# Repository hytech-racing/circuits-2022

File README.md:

# 2022 Circuits

Repository for all of the circuits for the 2021-2022 car.

## Getting Started with this Git Repository
1. Create a GitHub account if you don't already have one.
2. Follow HyTech's [Software Guide](https://github.com/hytech-racing/training/tree/master/Resources).
3. Download and install [GitHub Desktop](https://desktop.github.com/) (basic) or [Git CLI](https://git-scm.com/book/en/v2/Getting-Started-Installing-Git) (advanced).
    * If you are using GitHub Desktop for the first time, be sure to read the [User Guide](https://help.github.com/desktop/guides/).
    * If you are using Git for the first time, you should start off by reading a tutorial. There are many available online:
        * [Git Tutorial](https://git-scm.com/docs/gittutorial)
        * [Atlassian Git Tutorial](https://www.atlassian.com/git/tutorials/)
    * You may want to keep a copy of [GitHub's Git Cheat Sheet](https://services.github.com/kit/downloads/github-git-cheat-sheet.pdf) as a reference.
4. Talk to your subteam lead to be added to the team within the GitHub organization.
5. Clone this repository to your computer using the URLs:
    * SSH: `git@github.com:hytech-racing/circuits-2022.git`
    * HTTPS: `https://github.com/hytech-racing/circuits-2022.git`

## Getting Started with EAGLE
1. Follow HyTech's [Software Guide](https://github.com/hytech-racing/training/tree/master/Resources).
2. Download and install Autodesk [EAGLE](https://www.autodesk.com/products/eagle/overview)
3. Get the free [Educational License](https://www.autodesk.com/education/free-software/eagle) (a .edu email address is required)

## Github Software Guidelines and Electrical Designs Rules Review Process
Follow HyTech's [Github Software Guidelines](https://gtvault.sharepoint.com/:w:/r/sites/HyTechRacing2/Shared%20Documents/Electrical%20-%20All/HT06/Guidelines%20Rules%20and%20Procedures/Github%20Software%20Guidelines.docx?d=w7e0d7e36afeb47b5a935bd7a4851bceb&csf=1&web=1&e=sudzjV) to understand our development flow and pull request procedure.
Follow HyTech's [Electrical Designs Rules Review Process](https://gtvault.sharepoint.com/:w:/r/sites/HyTechRacing2/Shared%20Documents/Electrical%20-%20All/HT06/Guidelines%20Rules%20and%20Procedures/Electrical%20Designs%20Rules%20Review%20Process.docx?d=w0277498dfb4b4b9fbfad0e5db8a187c8&csf=1&web=1&e=LDFCNz) to understand circuit design flow. 

## Circuit Board Versioning Scheme
* New boards must start their numbering at revision 1.
* Revision numbers must be incremented by 1 when a physical board is manufactured, but not at any other time.
* After a board is manufactured, the files corresponding to the manufactured version should not be modified.
* Circuit boards based off of a previous year's design should increment based off of the previous board's revision number.

## More Information
* [Software Guide](https://github.com/hytech-racing/training/tree/master/Resources)
* [Team Site](https://hytechracing.gatech.edu/)
* [Facebook](https://www.facebook.com/HyTechRacing/)
* [Instagram](https://www.instagram.com/hytech.racing/)
* [Engage](https://gatech.campuslabs.com/engage/organization/hytech-racing)

## License
This project is licensed under the GPL License v3.0. See the [LICENSE](LICENSE) file for more information.

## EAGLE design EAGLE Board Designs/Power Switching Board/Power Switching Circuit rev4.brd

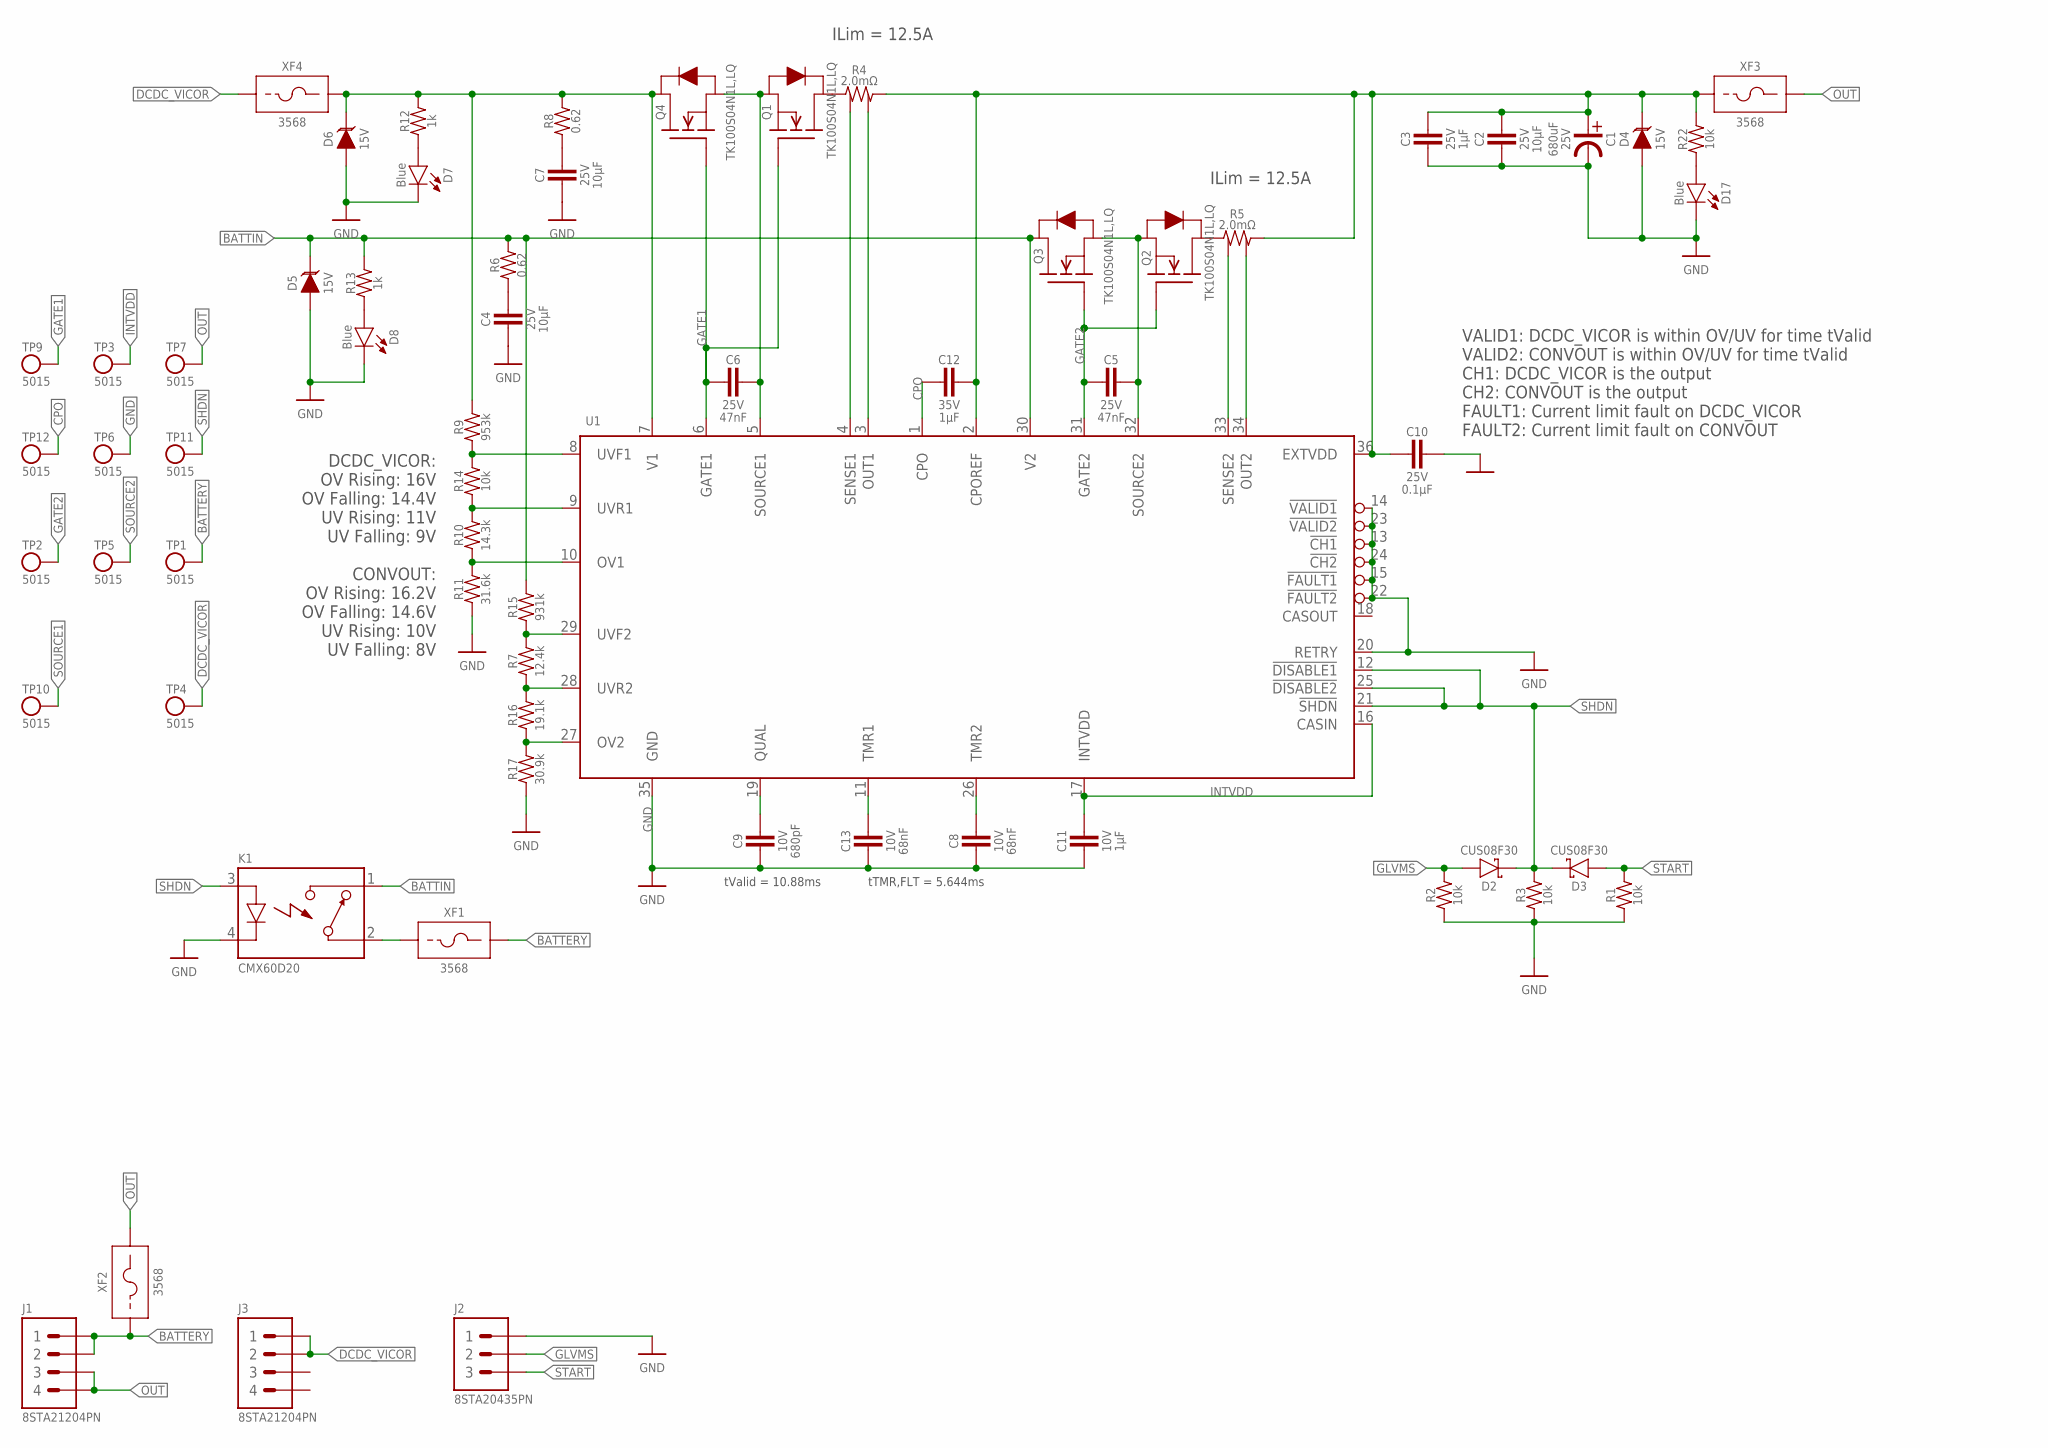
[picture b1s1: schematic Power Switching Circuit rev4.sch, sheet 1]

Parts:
C1: EEUFP1E681; EEUFP1E*
C2, C4, C7: CAPACITOR_0603_25V_10UF; 0603-CAP
C3: CAPACITOR_0603_25V_1UF; 0603-CAP
C5, C6: CAPACITOR_0603_25V_47NF; 0603-CAP
C8, C13: CAPACITOR_0603_10V_68NF; 0603-CAP
C9: CAPACITOR_0603_10V_680PF; 0603-CAP
C10: CAPACITOR_0603_25V_0.1UF; 0603-CAP
C11: CAPACITOR_0603_10V_1UF; 0603-CAP
C12: CAPACITOR_0603_35V_1UF; 0603-CAP
D2, D3: SCHOTTKY_SOD323_30V; SOD-323
D4, D5, D6: TVS_15V; SOT-23
D7, D8, D17: LED_0603_BLUE; 0603-LED
J1, J3: CONNECTOR-4_SOURIAU_; SOURIAU_12-04
J2: CONNECTOR-3_8STA20435PN; SOURIAU_04-35
K1: RELAY_SOLIDSTATE_NO_CMX60D20; CRYDOM_CMX
Q1, Q2, Q3, Q4: TRANSISTOR_N_MOS_2-7K1S_TK100S04N1LLQ; DPAK(2-7K1S)
R1, R2, R3, R14, R22: RESISTOR_0603_10K; 0603-RES
R4, R5: RESISTOR_SENSE__WSL40262L000FEB; 4026
R6, R8: RESISTOR_0805_0.62; 0805-RES
R7: RESISTOR_0603_12.4K; 0603-RES
R9: RESISTOR_0805_953K; 0805-RES
R10: RESISTOR_0805_14.3K; 0805-RES
R11: RESISTOR_0805_31.6K; 0805-RES
R12, R13: RESISTOR_0603_1K; 0603-RES
R15: RESISTOR_0805_931K; 0805-RES
R16: RESISTOR_0805_19.1K; 0805-RES
R17: RESISTOR_0603_30.9K; 0603-RES
TP1, TP2, TP4, TP5, TP6, TP7, TP9, TP10, TP11, TP12: TEST_POINT; 5015
TP3: INTVDD; 5015
U1: LTC4421; SSOP-36
XF1, XF2, XF3, XF4: FUSE_HOLDER_MINIBLADEPTH; 3568

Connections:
!SHDN: D2.C, D3.C, K1.3 (CONTROL+), R3.2, TP11.1, U1.12 (!DISABLE1), U1.21 (!SHDN), U1.25 (!DISABLE2)
BATTERY: J1.1, J1.2, TP1.1, XF1.3 (2), XF1.4 (2), XF2.1, XF2.2 (1)
BATTIN: D5.3 (C), K1.1 (CONTACT2), Q3.2 (D), R6.2, R13.2, R15.2, U1.30 (V2)
CPO: C12.2, TP12.1, U1.1 (CPO)
DCDC_VICOR: J3.1, J3.2, TP4.1, XF4.1, XF4.2 (1)
DCDC_VICORPREMOS: D6.3 (C), Q4.2 (D), R8.2, R9.2, R12.2, U1.7 (V1), XF4.3 (2), XF4.4 (2)
GATE1: C6.2, Q1.1 (G), Q4.1 (G), TP9.1, U1.6 (GATE1)
GATE2: C5.2, Q2.1 (G), Q3.1 (G), TP2.1, U1.31 (GATE2)
GLVMS: D2.A, J2.B (2), R2.2
GND: C1.P$2 (MINUS), C2.2, C3.2, C4.2, C7.2, C8.2, C9.2, C10.1, C11.2, C13.2, D4.1 (A), D5.1 (A), D6.1 (A), D7.1 (C), D8.1 (C), D17.1 (C), J2.A (1), K1.4 (CONTROL-), R1.1, R2.1, R3.1, R11.1, R17.1, TP6.1, U1.13 (!CH1), U1.14 (!VALID1), U1.15 (!FAULT1), U1.20 (RETRY), U1.22 (!FAULT2), U1.23 (!VALID2), U1.24 (!CH2), U1.35 (GND)
INTVDD: C11.1, TP3.1, U1.16 (CASIN), U1.17 (INTVDD)
unnamed: C9.1, U1.19 (QUAL)
unnamed: C13.1, U1.11 (TMR1)
unnamed: C8.1, U1.26 (TMR2)
unnamed: C4.1, R6.1
unnamed: D17.2 (A), R22.1
unnamed: D8.2 (A), R13.1
unnamed: D7.2 (A), R12.1
unnamed: K1.2 (CONTACT1), XF1.1, XF1.2 (1)
unnamed: R5.3, U1.33 (SENSE2)
unnamed: R5.4, U1.34 (OUT2)
unnamed: C7.1, R8.1
unnamed: R4.3, U1.4 (SENSE1)
unnamed: R10.2, R14.1, U1.9 (UVR1)
unnamed: R10.1, R11.2, U1.10 (OV1)
unnamed: R7.2, R15.1, U1.29 (UVF2)
unnamed: R7.1, R16.2, U1.28 (UVR2)
unnamed: R16.1, R17.2, U1.27 (OV2)
unnamed: Q2.2 (D), R5.1
unnamed: R4.4, U1.3 (OUT1)
unnamed: Q1.2 (D), R4.1
OUT: J1.3, J1.4, TP7.1, XF2.3 (2), XF2.4 (2), XF3.3 (2), XF3.4 (2)
OUTPREFUSE: C1.P$1 (PLUS), C2.1, C3.1, C10.2, C12.1, D4.3 (C), R4.2, R5.2, R22.2, U1.2 (CPOREF), U1.36 (EXTVDD), XF3.1, XF3.2 (1)
SOURCE1: C6.1, Q1.3 (S), Q4.3 (S), TP10.1, U1.5 (SOURCE1)
SOURCE2: C5.1, Q2.3 (S), Q3.3 (S), TP5.1, U1.32 (SOURCE2)
START: D3.A, J2.C (3), R1.2
UVF1: R9.1, R14.2, U1.8 (UVF1)

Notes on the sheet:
DCDC_VICOR: OV Rising: 16V OV Falling: 14.4V UV Rising: 11V UV Falling: 9V CONVOUT: OV Rising: 16.2V OV Falling: 14.6V UV Rising: 10V UV Falling: 8V
tValid = 10.88ms
tTMR,FLT = 5.644ms
ILim = 12.5A
VALID1: DCDC_VICOR is within OV/UV for time tValid VALID2: CONVOUT is within OV/UV for time tValid CH1: DCDC_VICOR is the output CH2: CONVOUT is the output FAULT1: Current limit fault on DCDC_VICOR FAULT2: Current limit fault on CONVOUT

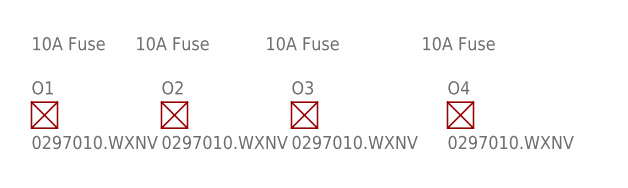
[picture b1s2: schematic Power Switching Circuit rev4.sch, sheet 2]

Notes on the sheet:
10A Fuse

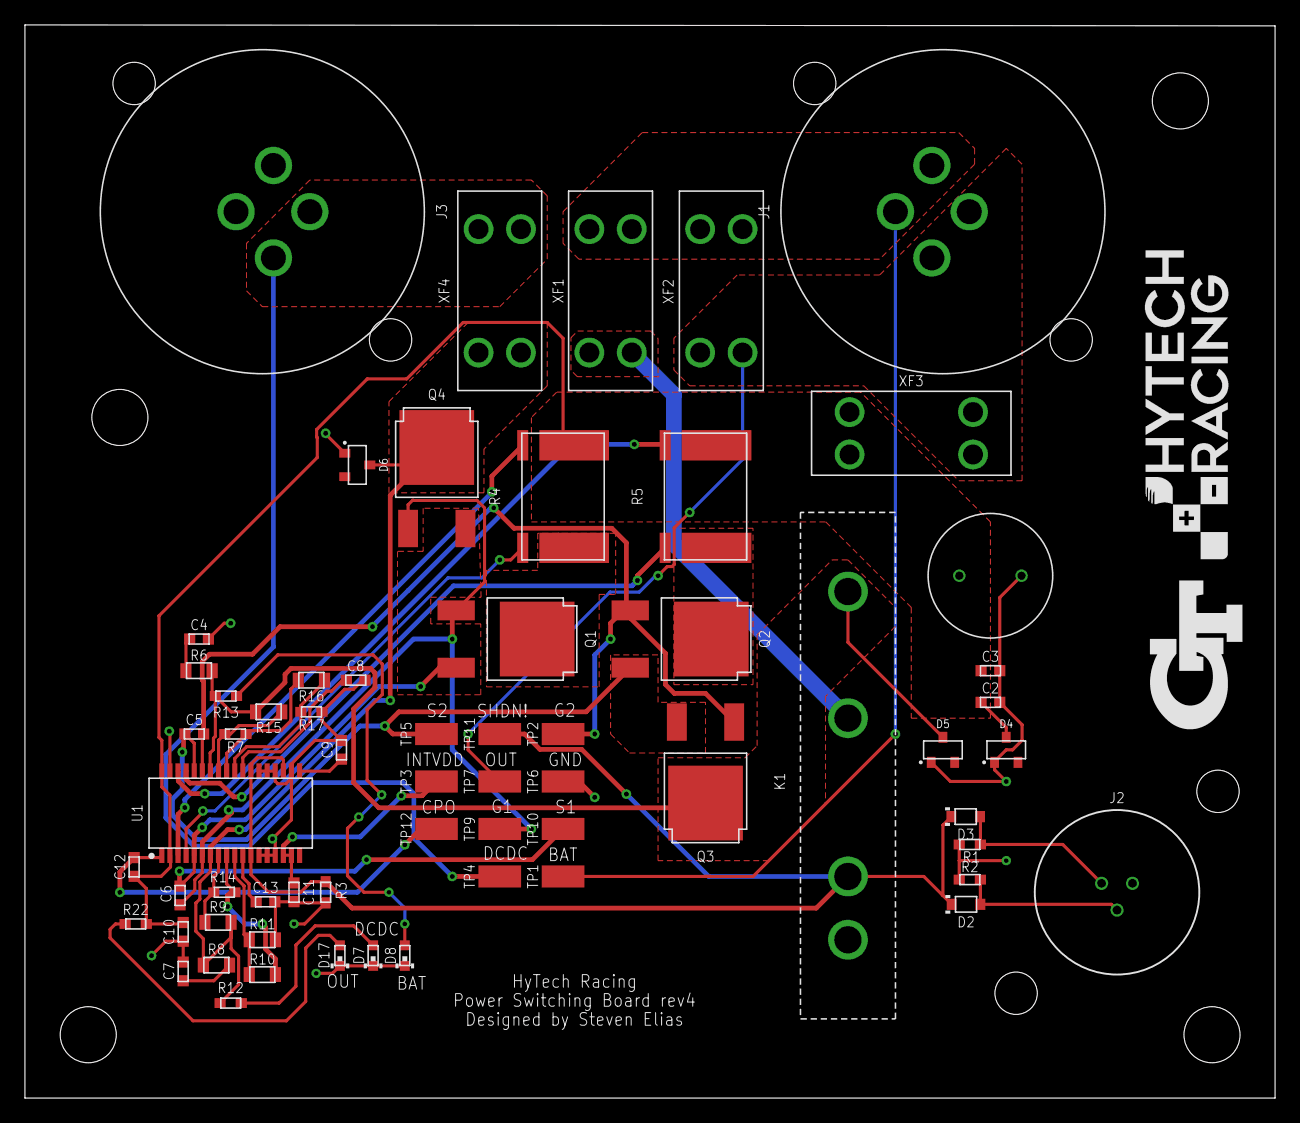
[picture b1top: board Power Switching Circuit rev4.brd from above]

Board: 2 copper layers, 100.3 x 86.1 mm, 69 parts (0 on the bottom side), 37 nets.

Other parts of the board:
U$1: LOGO_GT_MEDIUM
U$2: LOGO_HYTECH_MEDIUM
U$3, U$4, U$5, U$6: MOUNTING_M4

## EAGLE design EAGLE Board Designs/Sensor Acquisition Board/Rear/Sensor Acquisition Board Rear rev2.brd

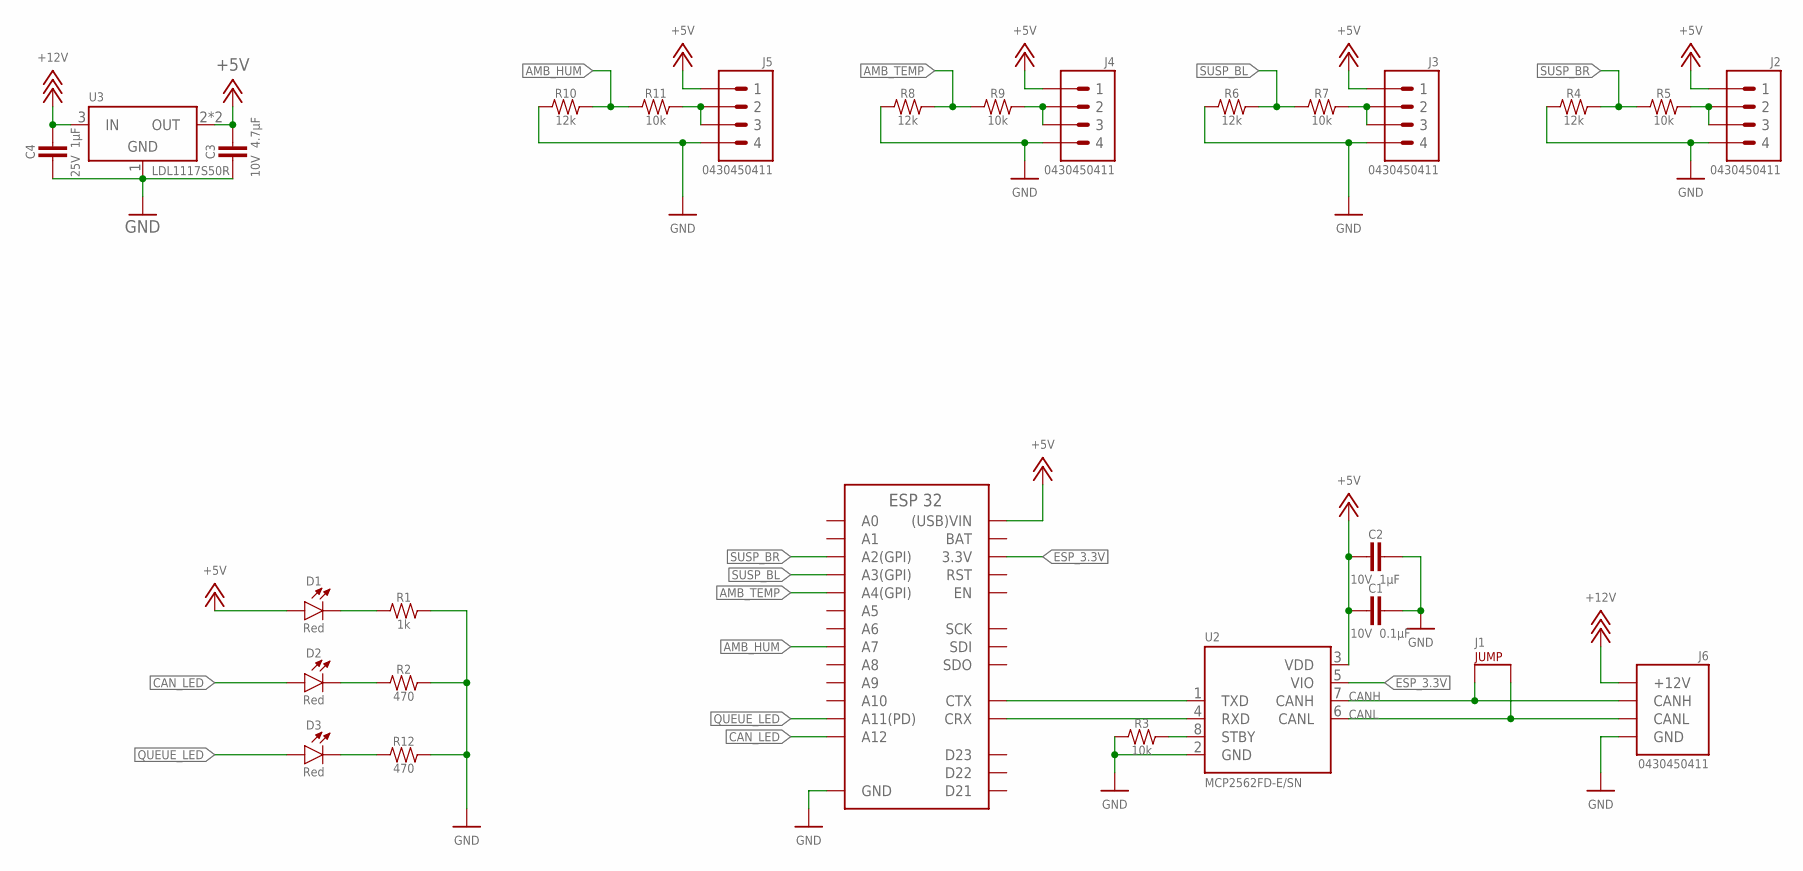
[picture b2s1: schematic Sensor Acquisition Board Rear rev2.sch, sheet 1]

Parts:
A2: ESP32
C1: CAPACITOR_0603_10V_0.1UF; 0603-CAP
C2: CAPACITOR_0603_10V_1UF; 0603-CAP
C3: CAPACITOR_0603_10V_4.7UF; 0603-CAP
C4: CAPACITOR_0603_25V_1UF; 0603-CAP
D1, D2, D3: LED_0603_RED; 0603-LED
J1: JUMPER_0603_; 0603-RES
J2, J3, J4, J5: CONNECTOR-4_μF_S_RA_; MOLEX_MICROFIT_SMD_RIGHTANGLE_04_DUAL
J6: CONNECTOR-CAN_μF_S_RA_; MOLEX_MICROFIT_SMD_RIGHTANGLE_04_DUAL
R1: RESISTOR_0603_1K; 0603-RES
R2, R12: RESISTOR_0603_470; 0603-RES
R3, R5, R7, R9, R11: RESISTOR_0603_10K; 0603-RES
R4, R6, R8, R10: RESISTOR_0603_12K; 0603-RES
U2: MCP2562FD; SOIC-08(NARROW,0.15")
U3: VOLTAGE_REGULATOR_SOT-223_5V; SOT-223

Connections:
+5V: A2.USB ((USB)VIN), C1.2, C2.2, C3.1, D1.2 (A), J2.1, J3.1, J4.1, J5.1, U2.3 (VDD), U3.2 (OUT), U3.4 (OUT)
+12V: C4.1, J6.1 (+12V), U3.3 (IN)
AMB_HUM: A2.D32 (A7), R10.2, R11.1
AMB_TEMP: A2.A4 (A4(GPI)), R8.2, R9.1
BAT: A2.BAT
CANH: J1.1, J6.4 (CANH), U2.7 (CANH)
CANL: J1.2, J6.3 (CANL), U2.6 (CANL)
CAN_LED: A2.D13 (A12), D2.2 (A)
EN: A2.EN
ESP_3.3V: A2.3.3V, U2.5 (VIO)
GND: A2.GND, C1.1, C2.1, C3.2, C4.2, J2.4, J3.4, J4.4, J5.4, J6.2 (GND), R1.2, R2.2, R3.1, R4.1, R6.1, R8.1, R10.1, R12.2, U2.2 (GND), U3.1 (GND)
unnamed: D1.1 (C), R1.1
unnamed: D2.1 (C), R2.1
unnamed: R3.2, U2.8 (STBY)
unnamed: A2.TX (CTX), U2.1 (TXD)
unnamed: J2.2, J2.3, R5.2
unnamed: J4.2, J4.3, R9.2
unnamed: J3.2, J3.3, R7.2
unnamed: A2.RX (CRX), U2.4 (RXD)
unnamed: J5.2, J5.3, R11.2
unnamed: D3.1 (C), R12.1
QUEUE_LED: A2.D12 (A11(PD)), D3.2 (A)
RST: A2.RST
SUSP_BL: A2.A3 (A3(GPI)), R6.2, R7.1
SUSP_BR: A2.A2 (A2(GPI)), R4.2, R5.1

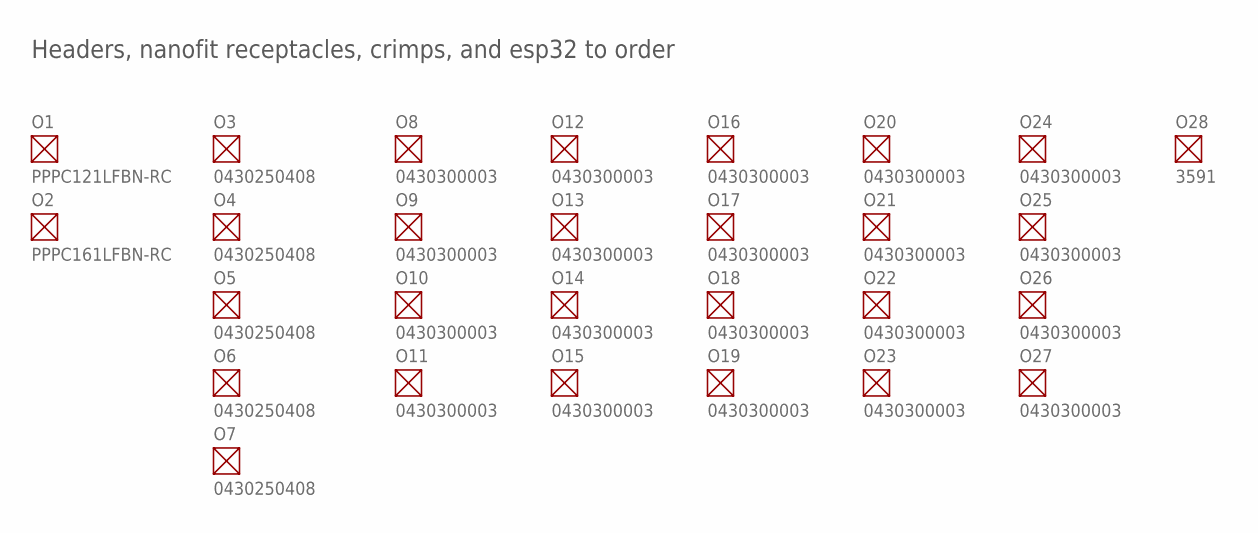
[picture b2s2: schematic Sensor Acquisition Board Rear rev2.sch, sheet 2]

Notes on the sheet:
Headers, nanofit receptacles, crimps, and esp32 to order

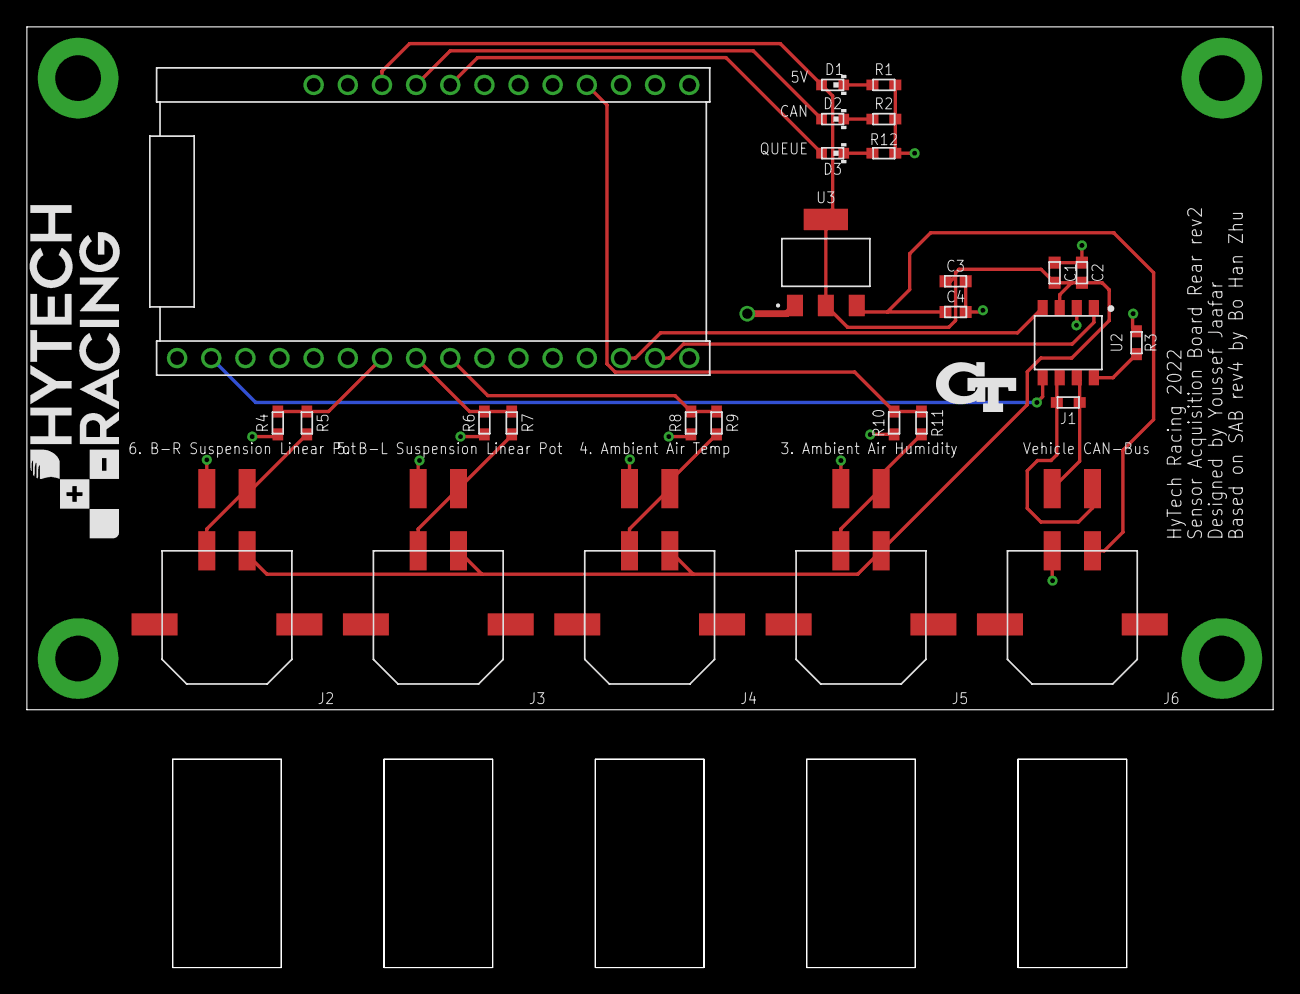
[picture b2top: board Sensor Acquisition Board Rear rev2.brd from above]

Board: 2 copper layers, 92.7 x 50.8 mm, 34 parts (0 on the bottom side), 22 nets.

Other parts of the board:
$$U$6: MOUNTING_M3
U$1, U$2, U$5: MOUNTING_M3
U$3: LOGO_GT_0.25"
U$4: LOGO_HYTECH_MEDIUM

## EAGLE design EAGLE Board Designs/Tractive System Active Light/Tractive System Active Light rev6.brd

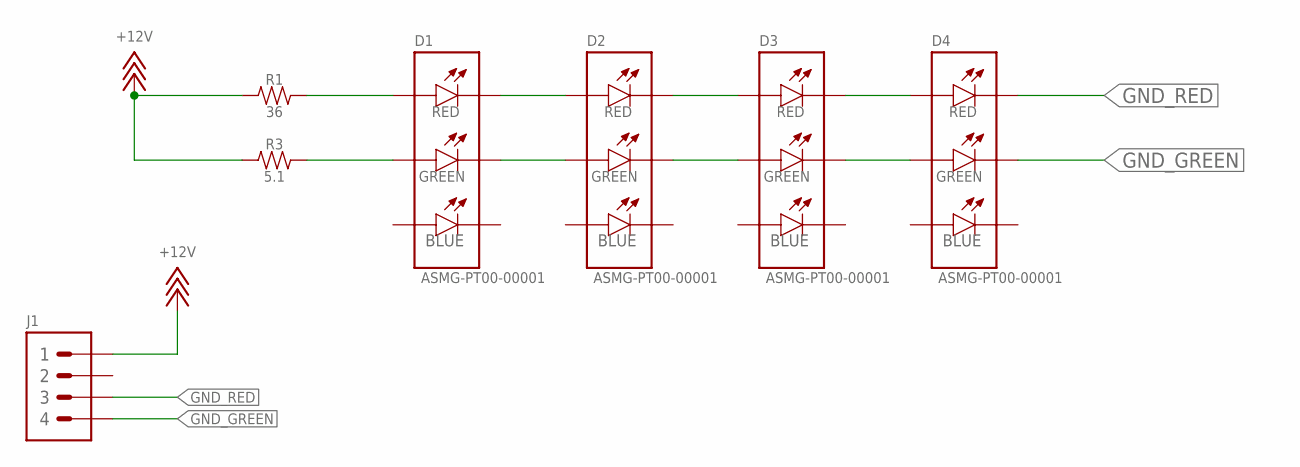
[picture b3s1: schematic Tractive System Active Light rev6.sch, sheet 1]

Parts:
D1, D2, D3, D4: LED_RGB_ASMG-PT00-00001; ASMG-PT00-00001
J1: CONNECTOR-4_μF_S_RA_; MOLEX_MICROFIT_SMD_RIGHTANGLE_04_DUAL
R1: RESISTOR_0805_36; 0805-RES
R3: RESISTOR_0805_5.1; 0805-RES

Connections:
+12V: J1.1, R1.1, R3.1
GND_GREEN: D4.2 (GREEN-), J1.4
GND_RED: D4.1 (RED-), J1.3
unnamed: D3.1 (RED-), D4.4 (RED+), D4.THERMAL (RED+)
unnamed: D3.2 (GREEN-), D4.5 (GREEN+)
unnamed: D2.1 (RED-), D3.4 (RED+), D3.THERMAL (RED+)
unnamed: D2.2 (GREEN-), D3.5 (GREEN+)
unnamed: D1.1 (RED-), D2.4 (RED+), D2.THERMAL (RED+)
unnamed: D1.2 (GREEN-), D2.5 (GREEN+)
unnamed: D1.4 (RED+), D1.THERMAL (RED+), R1.2
unnamed: D1.5 (GREEN+), R3.2

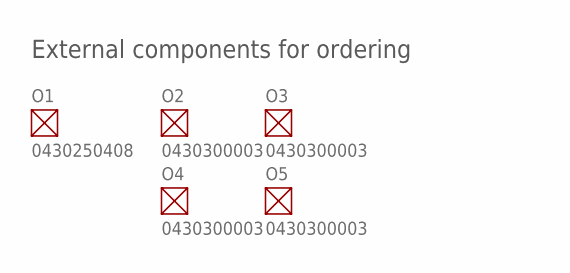
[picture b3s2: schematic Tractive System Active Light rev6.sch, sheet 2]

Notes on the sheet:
External components for ordering

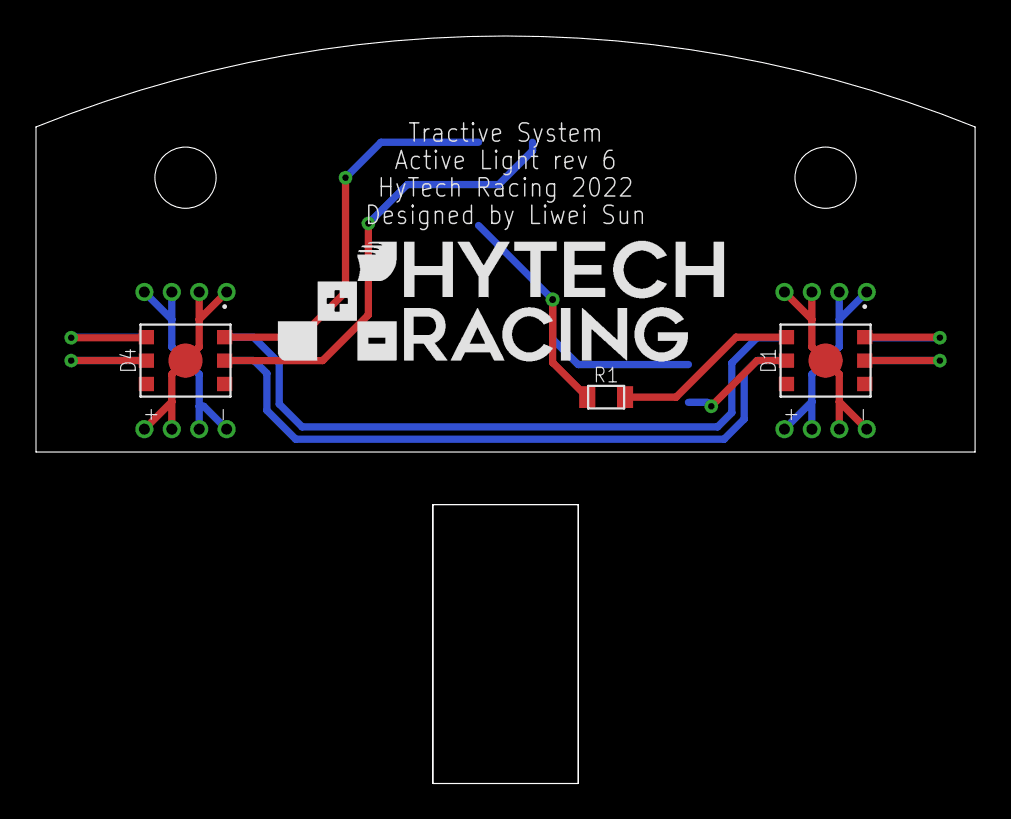
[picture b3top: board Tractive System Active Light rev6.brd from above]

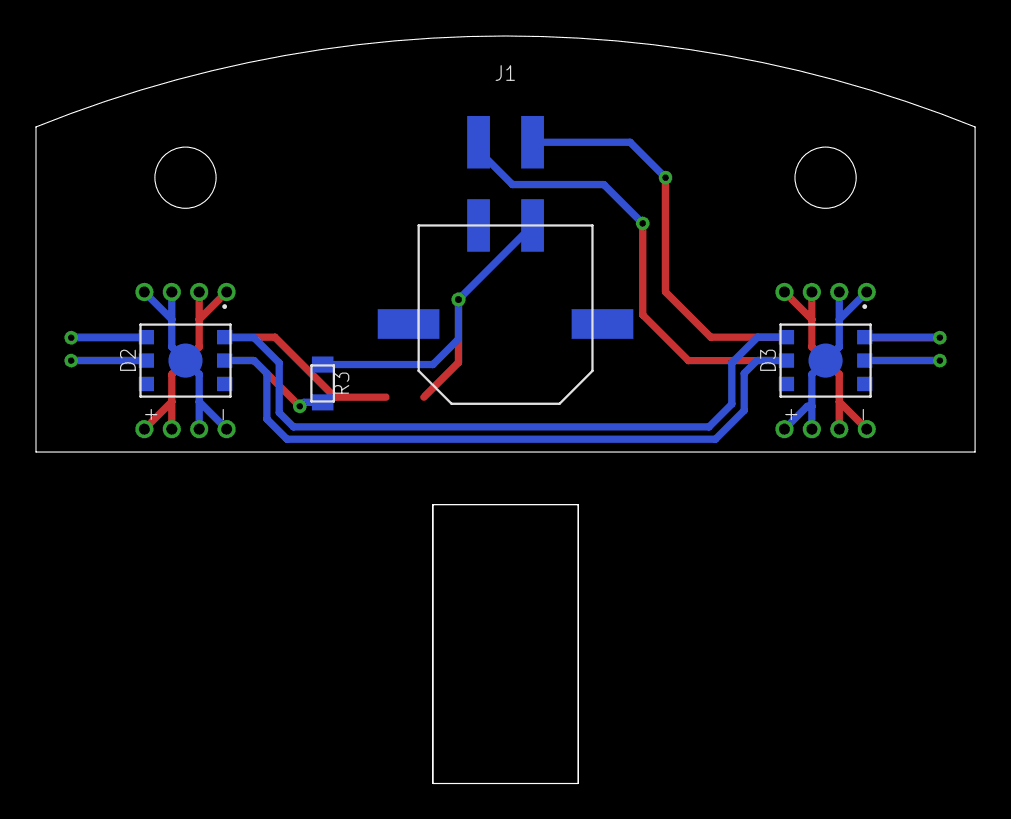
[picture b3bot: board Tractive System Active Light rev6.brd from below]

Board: 2 copper layers, 52.2 x 41.5 mm, 10 parts (4 on the bottom side), 11 nets.

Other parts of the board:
U$1, U$3: MOUNTING_M3
U$2: LOGO_HYTECH_MEDIUM

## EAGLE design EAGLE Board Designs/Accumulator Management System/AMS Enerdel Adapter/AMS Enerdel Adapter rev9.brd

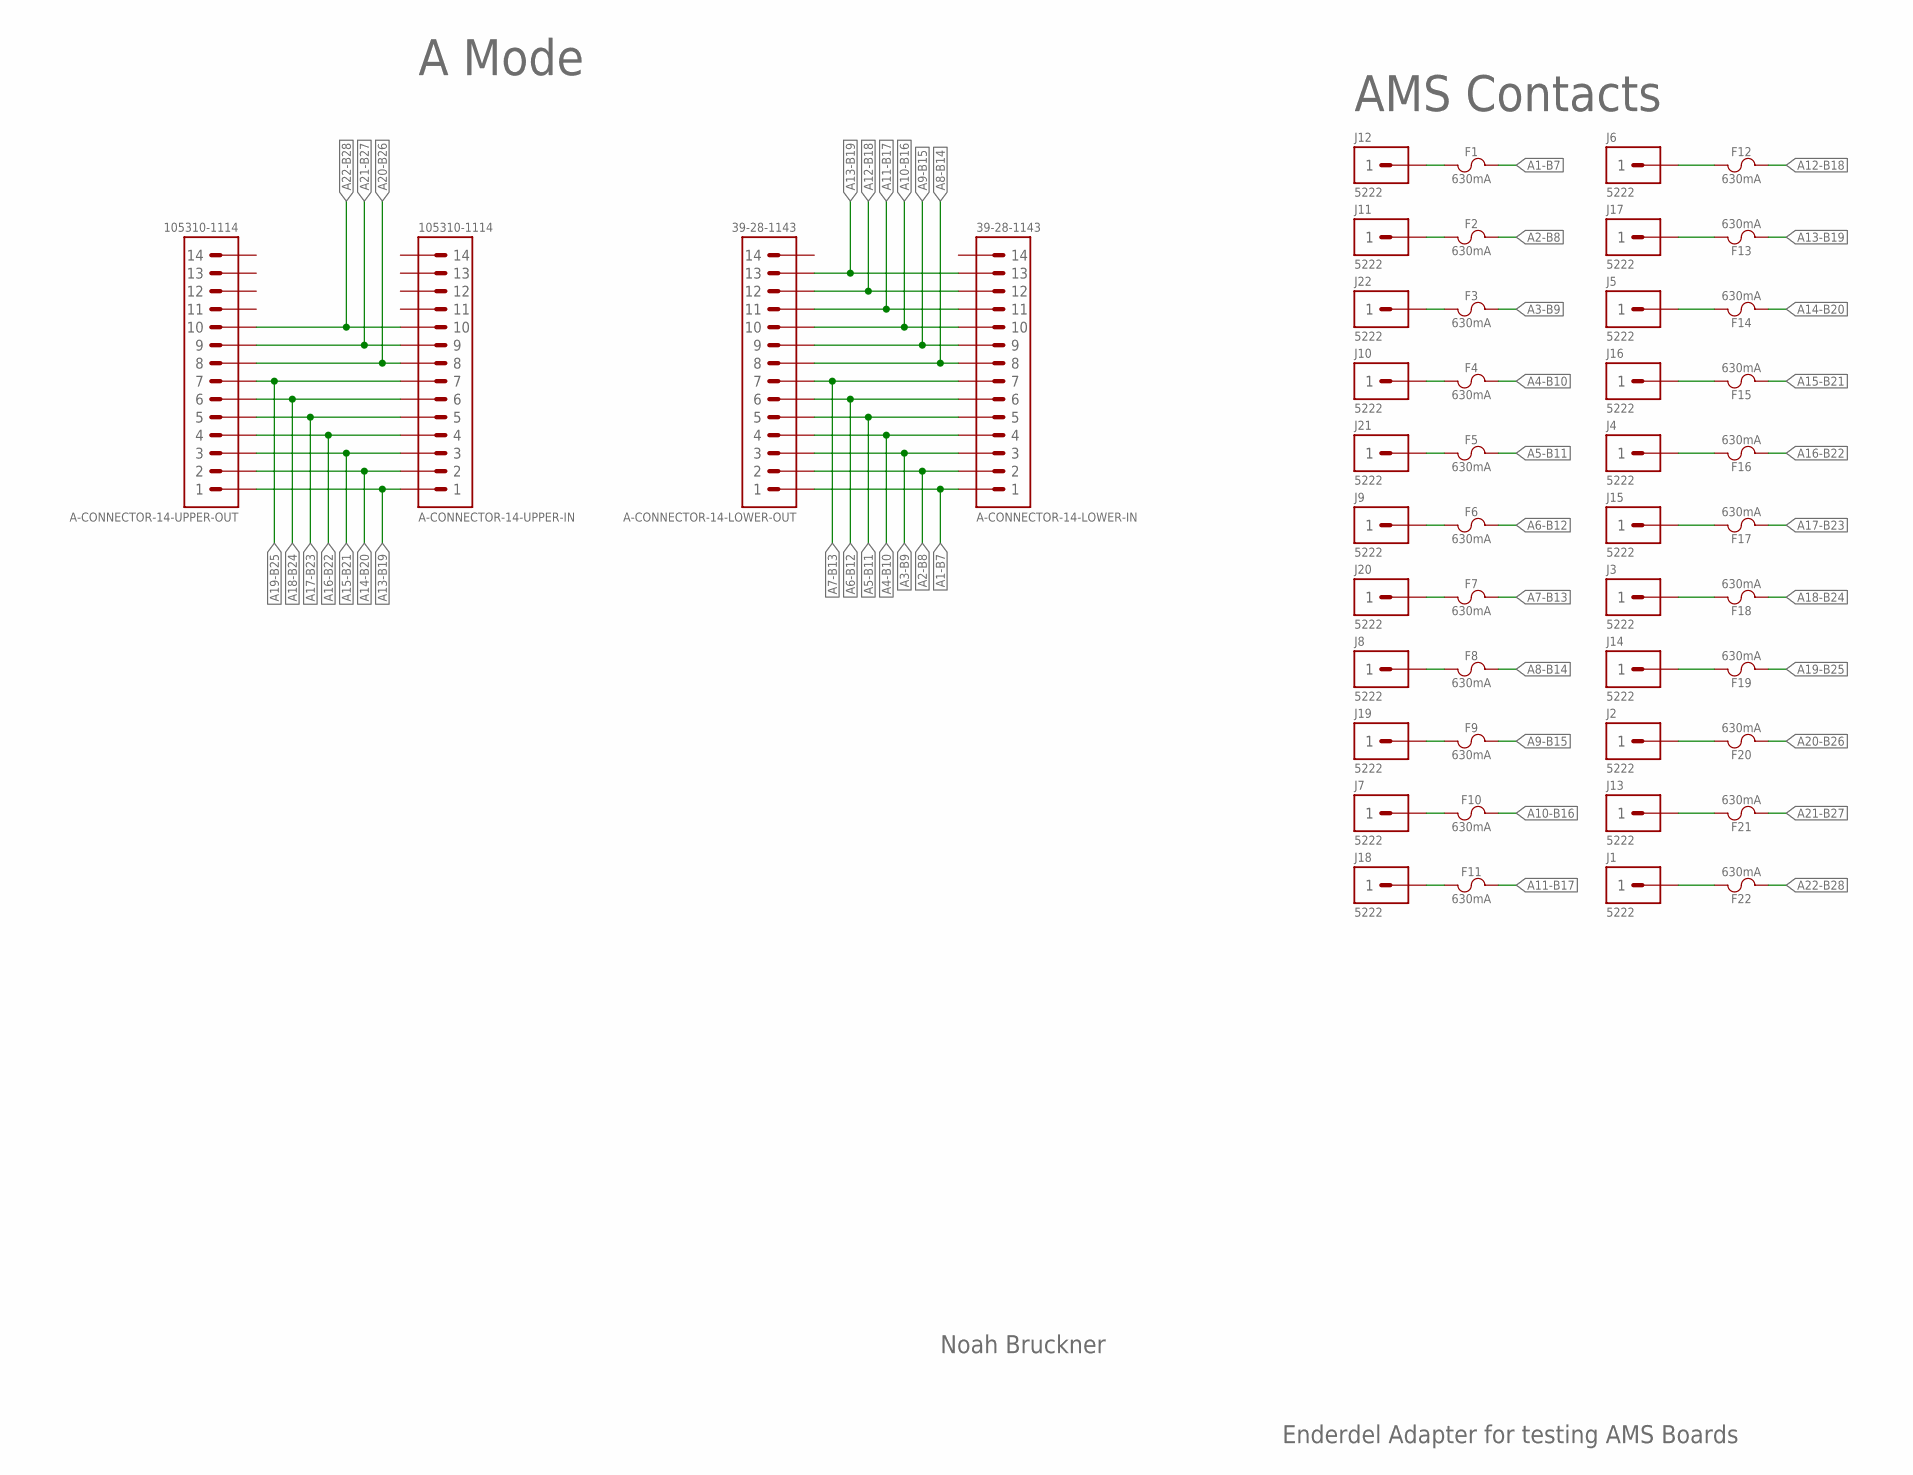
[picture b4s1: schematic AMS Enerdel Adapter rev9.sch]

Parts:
A-CONNECTOR-14-LOWER-IN, A-CONNECTOR-14-LOWER-OUT: CONNECTOR-14_MINIFIT_; MOLEX_MINIFIT_PTH_14; MPN 39-28-1143
A-CONNECTOR-14-UPPER-IN, A-CONNECTOR-14-UPPER-OUT: CONNECTOR-14_NANOFIT_; MOLEX_NANOFIT_PTH_14; MPN 105310-1114
F1, F2, F3, F4, F5, F6, F7, F8, F9, F10, F11, F12, F13, F14, F15, F16, F17, F18, F19, F20, F21, F22: FUSE_OMF_125_.63A; OMF_125
J1, J2, J3, J4, J5, J6, J7, J8, J9, J10, J11, J12, J13, J14, J15, J16, J17, J18, J19, J20, J21, J22: CONNECTOR-1_5222; 5222

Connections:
A1-B7: A-CONNECTOR-14-LOWER-IN.1, A-CONNECTOR-14-LOWER-OUT.1, F1.2
A2-B8: A-CONNECTOR-14-LOWER-IN.2, A-CONNECTOR-14-LOWER-OUT.2, F2.2
A3-B9: A-CONNECTOR-14-LOWER-IN.3, A-CONNECTOR-14-LOWER-OUT.3, F3.2
A4-B10: A-CONNECTOR-14-LOWER-IN.4, A-CONNECTOR-14-LOWER-OUT.4, F4.2
A5-B11: A-CONNECTOR-14-LOWER-IN.5, A-CONNECTOR-14-LOWER-OUT.5, F5.2
A6-B12: A-CONNECTOR-14-LOWER-IN.6, A-CONNECTOR-14-LOWER-OUT.6, F6.2
A7-B13: A-CONNECTOR-14-LOWER-IN.7, A-CONNECTOR-14-LOWER-OUT.7, F7.2
A8-B14: A-CONNECTOR-14-LOWER-IN.8, A-CONNECTOR-14-LOWER-OUT.8, F8.2
A9-B15: A-CONNECTOR-14-LOWER-IN.9, A-CONNECTOR-14-LOWER-OUT.9, F9.2
A10-B16: A-CONNECTOR-14-LOWER-IN.10, A-CONNECTOR-14-LOWER-OUT.10, F10.2
A11-B17: A-CONNECTOR-14-LOWER-IN.11, A-CONNECTOR-14-LOWER-OUT.11, F11.2
A12-B18: A-CONNECTOR-14-LOWER-IN.12, A-CONNECTOR-14-LOWER-OUT.12, F12.2
A13-B19: A-CONNECTOR-14-LOWER-IN.13, A-CONNECTOR-14-LOWER-OUT.13, A-CONNECTOR-14-UPPER-IN.1, A-CONNECTOR-14-UPPER-OUT.1, F13.1
A14-B20: A-CONNECTOR-14-UPPER-IN.2, A-CONNECTOR-14-UPPER-OUT.2, F14.1
A15-B21: A-CONNECTOR-14-UPPER-IN.3, A-CONNECTOR-14-UPPER-OUT.3, F15.1
A16-B22: A-CONNECTOR-14-UPPER-IN.4, A-CONNECTOR-14-UPPER-OUT.4, F16.1
A17-B23: A-CONNECTOR-14-UPPER-IN.5, A-CONNECTOR-14-UPPER-OUT.5, F17.1
A18-B24: A-CONNECTOR-14-UPPER-IN.6, A-CONNECTOR-14-UPPER-OUT.6, F18.1
A19-B25: A-CONNECTOR-14-UPPER-IN.7, A-CONNECTOR-14-UPPER-OUT.7, F19.1
A20-B26: A-CONNECTOR-14-UPPER-IN.8, A-CONNECTOR-14-UPPER-OUT.8, F20.1
A21-B27: A-CONNECTOR-14-UPPER-IN.9, A-CONNECTOR-14-UPPER-OUT.9, F21.1
A22-B28: A-CONNECTOR-14-UPPER-IN.10, A-CONNECTOR-14-UPPER-OUT.10, F22.1
unnamed: F1.1, J12.1
unnamed: F2.1, J11.1
unnamed: F3.1, J22.1
unnamed: F4.1, J10.1
unnamed: F5.1, J21.1
unnamed: F6.1, J9.1
unnamed: F7.1, J20.1
unnamed: F8.1, J8.1
unnamed: F9.1, J19.1
unnamed: F10.1, J7.1
unnamed: F11.1, J18.1
unnamed: F22.2, J1.1
unnamed: F21.2, J13.1
unnamed: F20.2, J2.1
unnamed: F19.2, J14.1
unnamed: F18.2, J3.1
unnamed: F17.2, J15.1
unnamed: F16.2, J4.1
unnamed: F15.2, J16.1
unnamed: F14.2, J5.1
unnamed: F12.1, J6.1
unnamed: F13.2, J17.1

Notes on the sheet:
Noah Bruckner
AMS Contacts
A Mode
Enderdel Adapter for testing AMS Boards

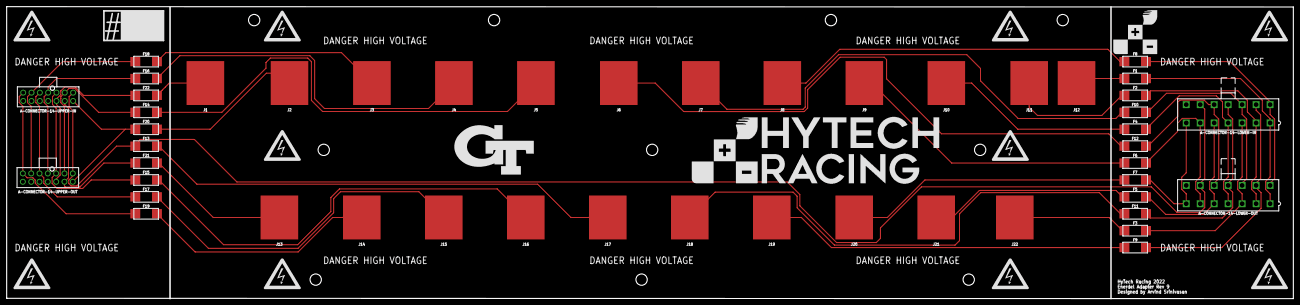
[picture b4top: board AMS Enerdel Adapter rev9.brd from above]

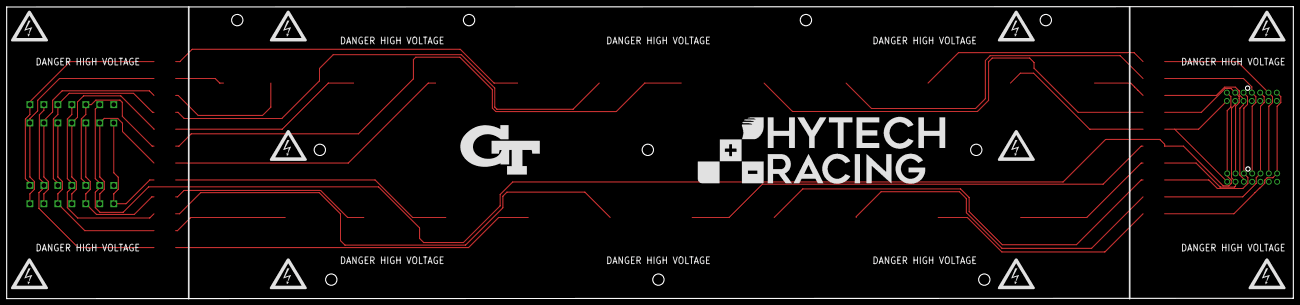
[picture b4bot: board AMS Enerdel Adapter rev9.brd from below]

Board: 2 copper layers, 386.6 x 87.7 mm, 94 parts (12 on the bottom side), 44 nets.

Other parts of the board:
U$1, U$2, U$3, U$4, U$20, U$21, U$22, U$29, U$30, U$31: MOUNTING_M3
U$5, U$6, U$12, U$13, U$14, U$18, U$23, U$24, U$26, U$28, U$35, U$36, U$37, U$38, U$39, U$40, U$41, U$42, U$43, U$44: HV_LARGE
U$7, U$8, U$9, U$10, U$11, U$15, U$19, U$25, U$27, U$34: DANGER_HIGH_VOLTAGE
U$16, U$46: LOGO_GT_LARGE
U$17: LOGO_HYTECH_SQUARE_EXTRA_LARGE
U$32, U$45: LOGO_HYTECH_EXTRA_LARGE
U$33: NUMBER
